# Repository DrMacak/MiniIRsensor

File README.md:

# MiniIRsensor
IR differential distance sensor board based on OrmerodSensorBoard David Crocker's desing.

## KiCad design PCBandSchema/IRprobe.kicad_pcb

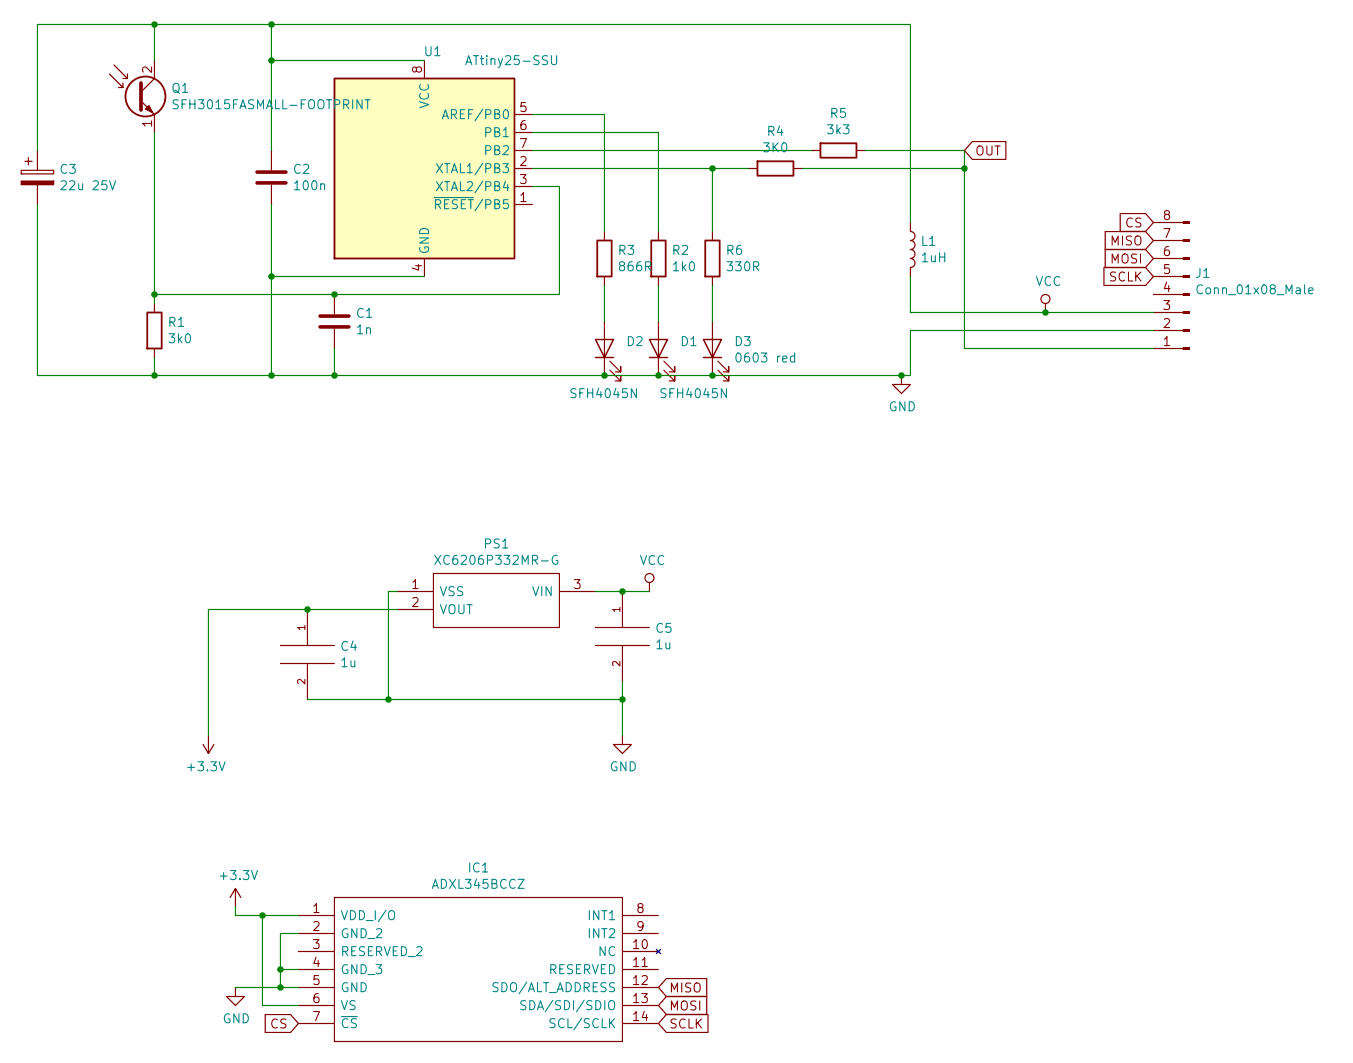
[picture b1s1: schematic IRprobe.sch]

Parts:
C1: 1n; C_0603_1608Metric
C2: 100n; C_0603_1608Metric
C3: 22u 25V; CP_Elec_4x5.4
C4, C5: 1u; C_0603_1608Metric
D1, D2: SFH4045N
D3: 0603 red; R_0603_1608Metric
IC1: ADXL345BCCZ; LGA14R80P3X6_300X500X100; Mouser Part Number N/A
J1: Conn_01x08_Male; PinHeader_2x04_P2.54mm_Vertical
L1: 1uH; LED_0603_1608Metric
PS1: XC6206P332MR-G; SOT95P280X130-3N; Mouser Part Number 865-XC6206P332MR-G
Q1: SFH3015FASMALL-FOOTPRINT; SFH3015FA
R1: 3k0; R_0603_1608Metric
R2: 1k0; R_0603_1608Metric
R3: 866R; R_0603_1608Metric
R4: 3K0; R_0603_1608Metric
R5: 3k3; R_0603_1608Metric
R6: 330R; R_0603_1608Metric
U1: ATtiny25-SSU; SOIC-8_3.9x4.9mm_P1.27mm

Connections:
+3V3: C4.1, IC1.1 (VDD_I/O), IC1.6 (VS), PS1.2 (VOUT)
CS: IC1.7 (~CS), J1.8
GND: C1.2, C2.2, C3.2, C4.2, C5.2, D1.1 (K), D2.1 (K), D3.1 (K), IC1.2 (GND_2), IC1.4 (GND_3), IC1.5 (GND), J1.2, PS1.1 (VSS), R1.2, U1.4 (GND)
MISO: IC1.12 (SDO/ALT_ADDRESS), J1.7
MOSI: IC1.13 (SDA/SDI/SDIO), J1.6
unnamed: C1.1, Q1.1 (E), R1.1, U1.3 (XTAL2/PB4)
unnamed: C2.1, C3.1, L1.1, Q1.2 (C), U1.8 (VCC)
unnamed: D1.2 (A), R2.2
unnamed: D2.2 (A), R3.2
unnamed: D3.2 (A), R6.2
unnamed: R2.1, U1.6 (PB1)
unnamed: R3.1, U1.5 (AREF/PB0)
unnamed: R4.2, R6.1, U1.2 (XTAL1/PB3)
unnamed: R5.2, U1.7 (PB2)
OUT: J1.1, R4.1, R5.1
SCLK: IC1.14 (SCL/SCLK), J1.5
VCC: C5.1, J1.3, L1.2, PS1.3 (VIN)

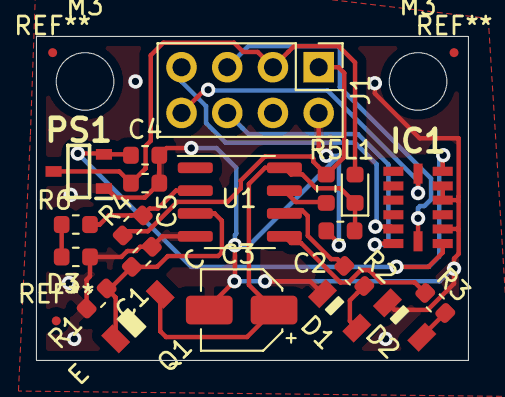
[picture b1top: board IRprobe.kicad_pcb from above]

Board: 2 copper layers, 24.0 x 18.0 mm, 22 parts (0 on the bottom side), 17 nets.

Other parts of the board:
M3, M3#2: MountingHole_3.2mm_M3

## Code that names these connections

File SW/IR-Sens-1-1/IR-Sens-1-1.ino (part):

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extern void sei();
#endif

#define ISR_DEBUG	(0)		// set nonzero to use PB2 as debug output pin

#define BITVAL(_x) static_cast<uint8_t>(1u << (_x))

// Pin assignments:
// PB0/MOSI			far LED drive, active high
// PB1/MISO			near LED drive, active high
// PB2/ADC1/SCK		output to Duet via 12K resistor
// PB3/ADC3			output to Duet via 10K resistor
// PB4/ADC2			input from phototransistor
// PB5/ADC0/RESET	not available, used for programming

#ifndef __ECV__
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
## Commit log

2022-09-27 Ver 2 Added ADXL
    Second version with same footprint but added ADXL on top of IR probe.

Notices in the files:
SW/IR-Sens-1-1/IR-Sens-1-1.ino:
Licensed under the GNU General Public License version 3. See http://www.gnu.org/licenses/gpl-3.0.en.html.
